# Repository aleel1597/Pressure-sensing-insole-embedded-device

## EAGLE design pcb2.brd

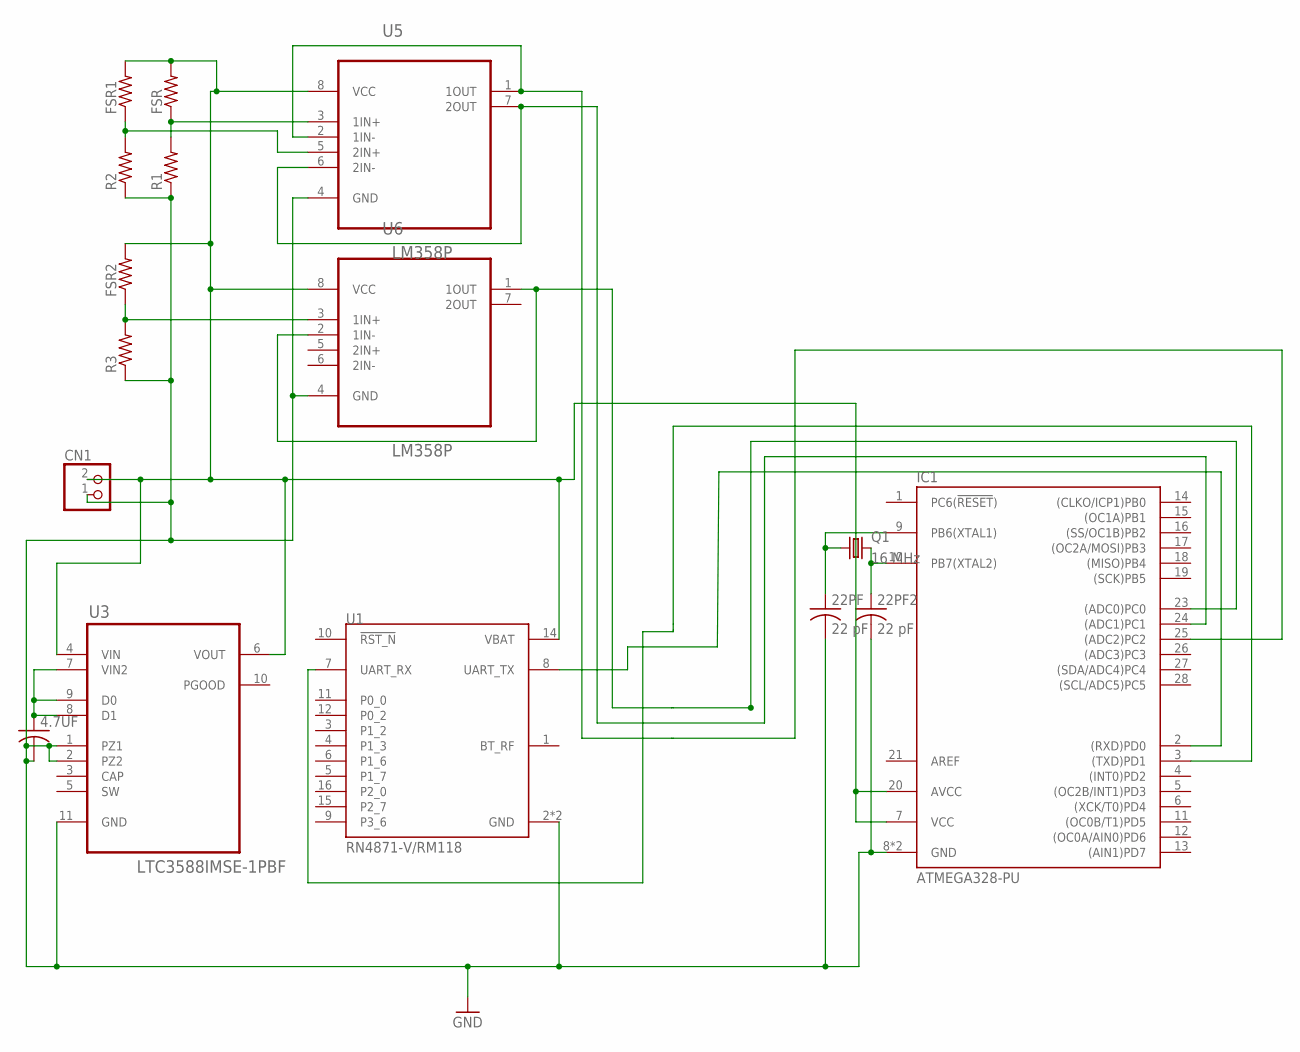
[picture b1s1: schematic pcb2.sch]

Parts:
4.7UF: C-US025-024X044; C025-024X044
22PF, 22PF2: 22 pF; C025-024X044
CN1: JST_2PIN-THM-RA; JST-PH-2-THM-RA
FSR, FSR1, FSR2: R-US_0204/5; 0204/5
IC1: ATMEGA328-PU; DIL28
Q1: 16 MHz; HC49U-V
R1, R2, R3: R-US_0204/5; 0204/5
U1: RN4871-V/RM118; XCVR_RN4871-V/RM118
U3: LTC3588IMSE-1PBF; SOP50P490X110-11N
U5, U6: LM358P; DIP254P762X508-8

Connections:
GND: 4.7UF.2, 22PF.2, 22PF2.2, CN1.1 (2), IC1.8 (GND), IC1.22 (GND), R1.1, R2.1, R3.1, U1.2 (GND), U1.13 (GND), U3.1 (PZ1), U3.2 (PZ2), U3.11 (GND), U5.4 (GND), U6.4 (GND)
unnamed: IC1.2 ((RXD)PD0), U1.8 (UART_TX)
unnamed: IC1.3 ((TXD)PD1), U1.7 (UART_RX)
unnamed: CN1.2 (1), FSR.2, FSR1.2, FSR2.2, IC1.7 (VCC), IC1.20 (AVCC), U1.14 (VBAT), U3.4 (VIN), U3.6 (VOUT), U5.8 (VCC), U6.8 (VCC)
unnamed: FSR2.1, R3.2, U6.3 (1IN+)
unnamed: IC1.23 ((ADC0)PC0), U6.1 (1OUT), U6.2 (1IN-)
unnamed: FSR.1, R1.2, U5.3 (1IN+)
unnamed: IC1.25 ((ADC2)PC2), U5.1 (1OUT), U5.2 (1IN-)
unnamed: IC1.24 ((ADC1)PC1), U5.6 (2IN-), U5.7 (2OUT)
unnamed: FSR1.1, R2.2, U5.5 (2IN+)
unnamed: 4.7UF.1, U3.7 (VIN2), U3.8 (D1), U3.9 (D0)
unnamed: 22PF.1, IC1.9 (PB6(XTAL1)), Q1.1
unnamed: 22PF2.1, IC1.10 (PB7(XTAL2)), Q1.2

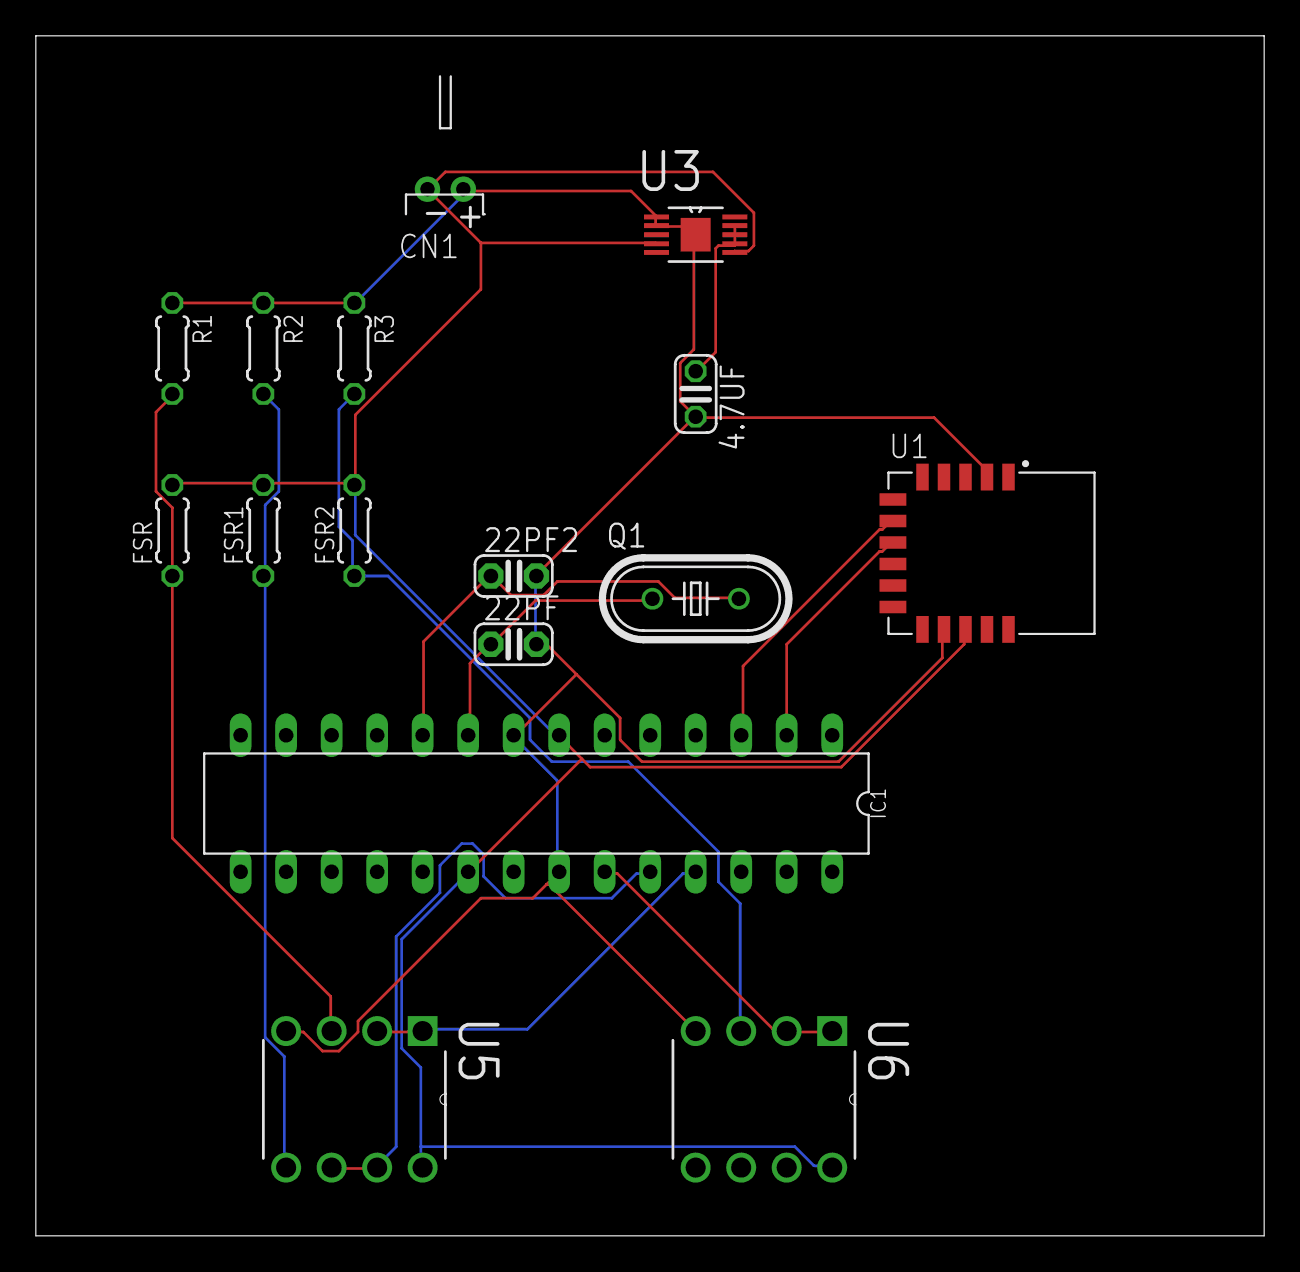
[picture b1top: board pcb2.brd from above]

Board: 2 copper layers, 68.6 x 67.0 mm, 16 parts (0 on the bottom side), 13 nets.
